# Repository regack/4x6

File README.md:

4x6
===

4x6  or 4x5 Keypad

Based on GH60 Rev B

## 4x5 variant
* removed references to bottom row

## v0.12.1
* cleaned up silkscreen some more after receiving pcbwing prototypes...

## v0.10-0.12
* cleaned up silkscreen to make everything visible
* fixed not-connected pads (oops)
* fixed BOM entries for items
* fixed diode pads to work with SOD-123 package
* extended USB pads for easier soldering
* added support for MCP23018 serial IO expander
* other stuff I probably forgot since I'm bad at checking stuff in

###  MATRIX (ATMEGA)

* ROW1 = PD0 / pin 18
* ROW2 = PD1 / pin 19
* ROW3 = PD2 / pin 20
* ROW4 = PD3 / pin 21
* ROW5 = PD4 / pin 25
* ROW6 = PD5 / pin 22

* COL1 = PF0 / pin 41
* COL2 = PF1 / pin 40
* COL3 = PE6 / pin 1
* COL4 = PC7 / pin 32

### MATRIX (MCP23018)
* ROW1 = GPB5 / pin 7
* ROW2 = GPB4 / pin 6
* ROW3 = GPB3 / pin 5
* ROW4 = GPB2 / pin 4
* ROW5 = GPB1 / pin 3
* ROW6 = GPB0 / pin 2

* COL1 = GPA0 / pin 17
* COL2 = GPA1 / pin 18
* COL3 = GPA2 / pin 19
* COL4 = GPA3 / pin 20

### LEDs
* NUMLOCK = PB2 / pin 10
* DF1 = PF7 / pin 36
* DF2 = PF6 / pin 37
* DF3 = PF5 / pin 38

## v0.9
* cleaned up silkscreens and added notes
* rotated S51 and S21
* added mounting holes (5)
* minor placement tweaks

## v0.8
* 1.27mm headers on left-board edge for ROWS, COLUMNS, Vcc, GND and Fn/NumLock LED control line
* silkscreen on back for headers
* geekhack silkscreen
* adjusted spacing of breakaway drill holes 
* still need to fix pad interference of S5 and S21
* might ditch mounting slot on left-edge of board

## v0.5
* Cleaned up silkscreen text and locations

## v0.4
* Added additional 'breakaway' holes
* Fixed S51 and S21 drill hole collisions (rotate 180)
* Added slotted mouting holes in center of board
* Aligned 'reset' switch properly
* Cleaned up measurement lines
* Cleaned up top and bottom ground zones

## v0.3
* Includes additional key positions and working on breakaway bottom row
* Added 'breakaway' holes for easier removal of the bottom row

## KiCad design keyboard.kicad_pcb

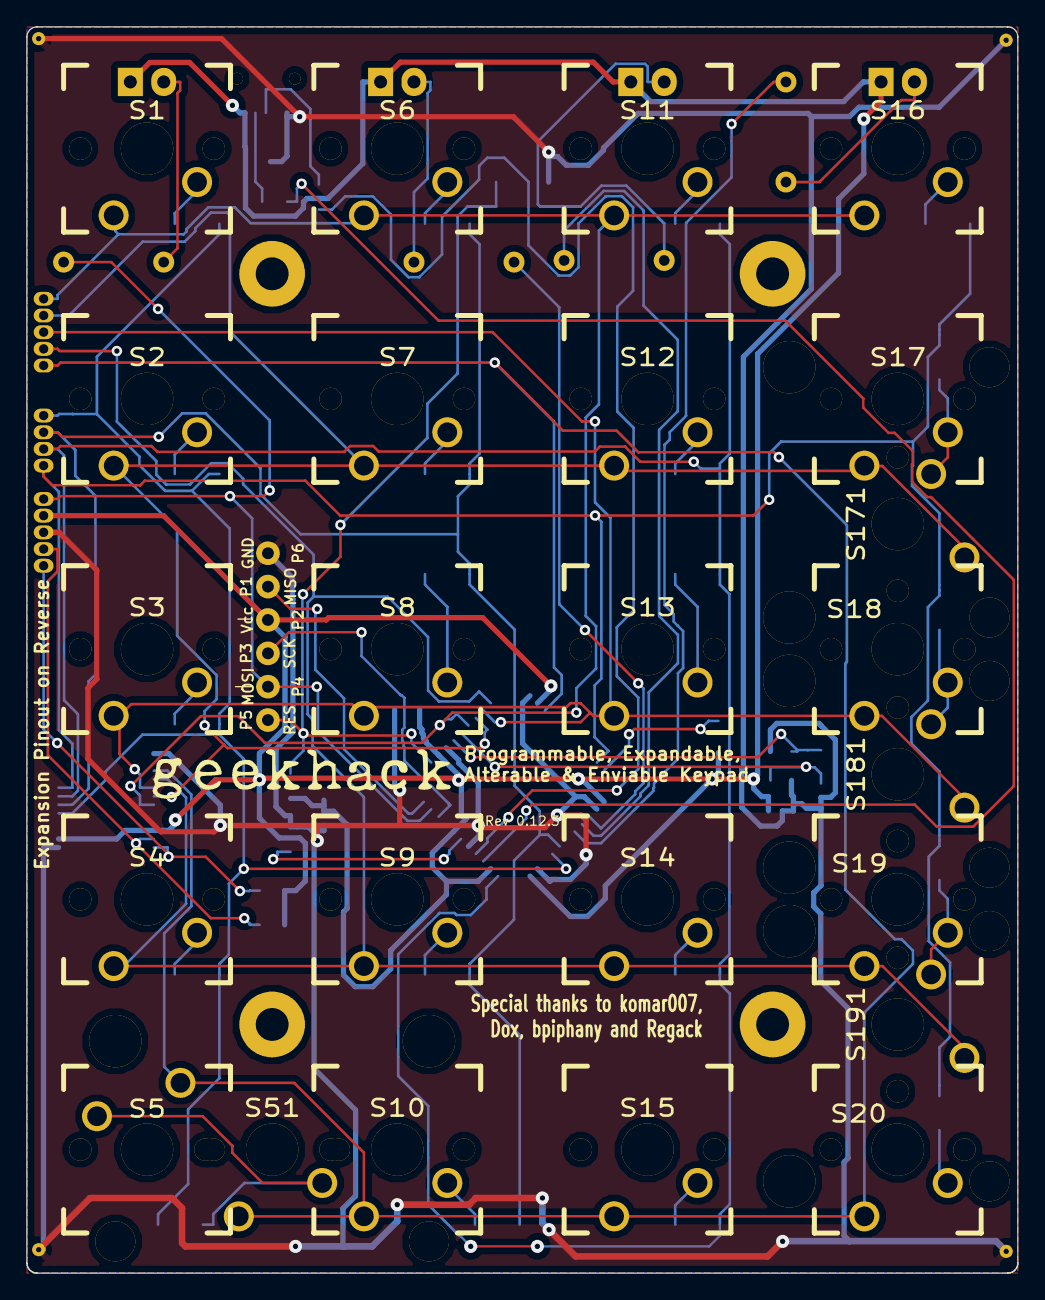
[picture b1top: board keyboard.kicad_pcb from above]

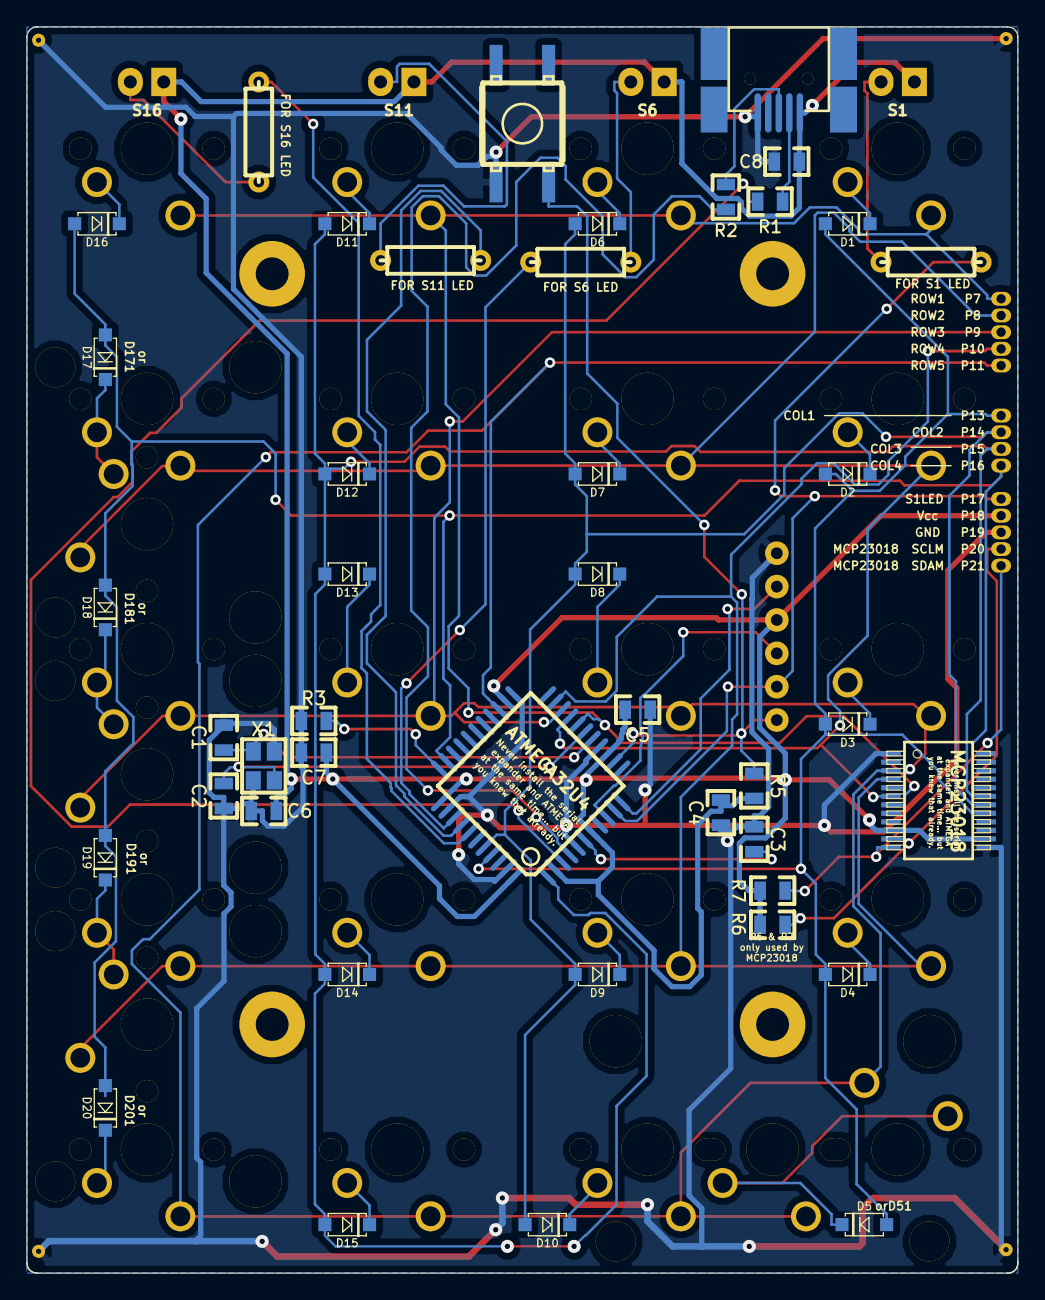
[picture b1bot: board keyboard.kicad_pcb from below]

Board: 2 copper layers, 75.4 x 94.9 mm, 100 parts (57 on the bottom side), 52 nets.

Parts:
C1, C2: 22pF; SM0805
C3, C8: 1uF; SM0805
C4, C5, C6, C7: 0.1uF; SM0805
D1, D2, D3, D4, D5, D6, D7, D8, D9, D10, D11, D12, D13, D14, D15, D16, D17, D18, D19, D20: 1N4148; SOD-123(A-C)
DC1: LED; MX_LED
DF1, DF2, DF3: LED; MX_LED
H1, H2, H3, H4: HOLE; Mechanical_Hole
IC1: ATMEGA32U4; TQFP44
J1: USB MINI-B; USB_MINI-B_MOLEX_67503-1020
LOGO1: Geekhack; LOGO
P1: MISO; pad
P2: Vcc; pad
P3: SCK; pad
P4: MOSI; pad
P5: RES; pad
P6: GND; pad
P7: ROW1; Pad_50mil
P8: ROW2; Pad_50mil
P9: ROW3; Pad_50mil
P10: ROW4; Pad_50mil
P11: ROW5; Pad_50mil
P13: COL1; Pad_50mil
P14: COL2; Pad_50mil
P15: COL3; Pad_50mil
P16: COL4; Pad_50mil
P17: FNLED; Pad_50mil
P18: Vcc; Pad_50mil
P19: GND; Pad_50mil
P20: SCLM; Pad_50mil
P21: SDAM; Pad_50mil
P200, P201, P202, P203: GND; Pad_Gnd
R1, R2: 22Ω; SM0805
R3, R5: 10kΩ; SM0805
R4: kΩ; R3
R6, R7: 2.2kΩ; SM0805
RF1, RF2, RF3: kΩ; R3
S0: ADTSMW69NVTR; KSEM31GLFS
S1, S2, S3, S4, S5, S6, S7, S8, S9, S10, S11, S12, S13, S14, S15, S16, S17, S18, S19, S20: MX1A; CHERRY_PCB_100H_Plated
S51, S171, S181, S191: MX1A; CHERRY_PCB_200H_Visible
U1: MCP23018; adafruit-SSOP24
X1: 7M-16.000MAAJ-T; ASX3F

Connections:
/GPIO0: IC1.36, RF1.1
/GPIO1: IC1.37, RF2.1
/GPIO2: IC1.38, RF3.1
/MISO: IC1.11, P1.1
/Matrix/col1: D1.A, D2.A, D3.A, D4.A, D5.A, IC1.41, P13.1, U1.17
/Matrix/col2: D6.A, D7.A, D8.A, D9.A, D10.A, IC1.40, P14.1, U1.18
/Matrix/col3: D11.A, D12.A, D13.A, D14.A, D15.A, IC1.1, P15.1, U1.19
/Matrix/col4: D16.A, D17.A, D18.A, D19.A, D20.A, IC1.32, P16.1, U1.20
/Matrix/numlock: IC1.10, P4.1, P17.1, R4.2
/Matrix/row1: IC1.18, P7.1, S1.1, S6.1, S11.1, S16.1, U1.7
/Matrix/row2: IC1.19, P8.1, S2.1, S7.1, S12.1, S17.1, S171.1, U1.6
/Matrix/row3: IC1.20, P9.1, S3.1, S8.1, S13.1, S18.1, S181.1, U1.5
/Matrix/row4: IC1.21, P10.1, S4.1, S9.1, S14.1, S19.1, S191.1, U1.4
/Matrix/row5: IC1.25, P11.1, S5.1, S10.1, S15.1, S20.1, S51.1, U1.3
/SCK: IC1.9, P3.1
/SCLM: P20.1, R6.2, U1.11
/SDAM: P21.1, R7.2, U1.12
/~RES~: IC1.13, P5.1, R5.2, S0.3
GND: C1.2, C2.2, C3.2, C4.2, C5.2, C6.2, C7.2, C8.2, IC1.5, IC1.15, IC1.23, IC1.35, IC1.43, J1.5, P6.1, P19.1, P200.1, P201.1, P202.1, P203.1, R3.2, S0.1, U1.1, U1.13, X1.2, X1.4
unnamed: DF2.2, RF2.2
unnamed: DF1.2, RF1.2
unnamed: DF3.2, RF3.2
unnamed: C1.1, IC1.16, X1.1
unnamed: IC1.33, R3.1
unnamed: C2.1, IC1.17, X1.3
unnamed: C3.1, IC1.6
unnamed: IC1.4, R2.1
unnamed: J1.3, R2.2
unnamed: J1.2, R1.2
unnamed: IC1.3, R1.1
unnamed: D15.C, S15.2
unnamed: D10.C, S10.2
unnamed: D3.C, S3.2
unnamed: D4.C, S4.2
unnamed: D20.C, S20.2
unnamed: D5.C, S5.2, S51.2
unnamed: D19.C, S19.2, S191.2
unnamed: D17.C, S17.2, S171.2
unnamed: D18.C, S18.2, S181.2
unnamed: D12.C, S12.2
unnamed: D7.C, S7.2
unnamed: D2.C, S2.2
unnamed: D11.C, S11.2
unnamed: D6.C, S6.2
unnamed: D1.C, S1.2
unnamed: D16.C, S16.2
unnamed: D8.C, S8.2
unnamed: D13.C, S13.2
unnamed: D9.C, S9.2
unnamed: D14.C, S14.2
unnamed: DC1.2, R4.1
VCC: C4.1, C5.1, C6.1, C7.1, C8.1, DC1.1, DF1.1, DF2.1, DF3.1, IC1.2, IC1.7, IC1.14, IC1.24, IC1.34, IC1.44, J1.1, P2.1, P18.1, R5.1, R6.1, R7.1, U1.10, U1.14

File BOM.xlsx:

ref | value | Quantity | datasheet | footprint | Field2 | Field3
C1,C2 | 22pF | 2 |  | 804 | VJ0805A220GXXCW1BC | https://www.mouser.com/Search/ProductDetail.aspx?R=VJ0805A22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
C3 | 1uF | 1 |  | 805 | VJ0805Y105JXQTW1BC | https://www.mouser.com/Search/ProductDetail.aspx?R=VJ0805Y10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
C4..C7 | 0.1uF | 4 |  | 805 | VJ0805Y104JXXAC | https://www.mouser.com/Search/ProductDetail.aspx?R=VJ0805Y10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
C8 | 1uF | 1 |  | 805 | VJ0805Y105JXQTW1BC | https://www.mouser.com/Search/ProductDetail.aspx?R=VJ0805Y10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
D1..D24 | 1N4148 | 24 |  | SOD-123 | 1N4148
DC1..DF3 | LED | 4
IC1 | ATMEGA32U4 | 1 |  | TQFP44 | ATmega32U4-AU | https://www.mouser.com/Search/ProductDetail.aspx?R=ATMEGA32U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
J1 | USB MINI-B | 1 |  |  | Molex 67503-1020
R1,R2 | 22Ω | 2 |  | 805 | CRCW080522R0JNTABC
R3 | 10kΩ | 1 |  | 805 | CRCW080510K0FKEB | https://www.mouser.com/Search/ProductDetail.aspx?R=CRCW08051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
R4 | kΩ | 1 | Value depends on DC1 LED | through-hole
R5 | 10kΩ | 1 |  | 805 | CRCW080510K0FKEB | https://www.mouser.com/Search/ProductDetail.aspx?R=CRCW08051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
R6,R7 | 2.2kΩ | 2 |  | 805 | CRCW08052K20JNEA | https://www.mouser.com/Search/ProductDetail.aspx?R=CRCW08052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
RF1 | kΩ | 1 | Value depends on DF1 LED | through-hole
RF2 | kΩ | 1 | Value depends on DF2 LED | through-hole
RF3 | kΩ | 1 | Value depends on DF3 LED | through-hole
S0 | ADTSMW69NVTR | 1 |  | switch-tact-DTSM-6 | TACTB-64K-F
S1..S211 | MX1A | 30 |  |  | CHERRY MX
U1 | MCP23018 | 1 |  | SSOP24 | MCP23018-E/SS | https://www.mouser.com/Search/ProductDetail.aspx?R=MCP23018-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
X1 | 7M-16.000MAAJ-T | 1 | Crystal |  | 7M-16.000MAAJ-T | https://www.mouser.com/Search/ProductDetail.aspx?R=7M-16.000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

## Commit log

2013-09-17 Initial Revision
2013-09-17 v0.2
2013-09-18 parts list
2013-09-18 v0.3
2013-09-19 bill of materials
2013-09-24 v0.4
2013-09-24 Spacing
2013-09-24 v0.5
2013-10-17 v0.8
2013-10-20 v0.9
2013-11-25 v0.12
2013-11-26 fixed formatting
2013-12-17 v0.12.1
2013-12-17 4x5 variant
2014-01-01 v0.12.2
2014-01-02 fixed silkscreen
2014-02-12 v0.12.3
2014-02-19 firmware
2014-02-19 fixed readme
2014-02-20 compiled
